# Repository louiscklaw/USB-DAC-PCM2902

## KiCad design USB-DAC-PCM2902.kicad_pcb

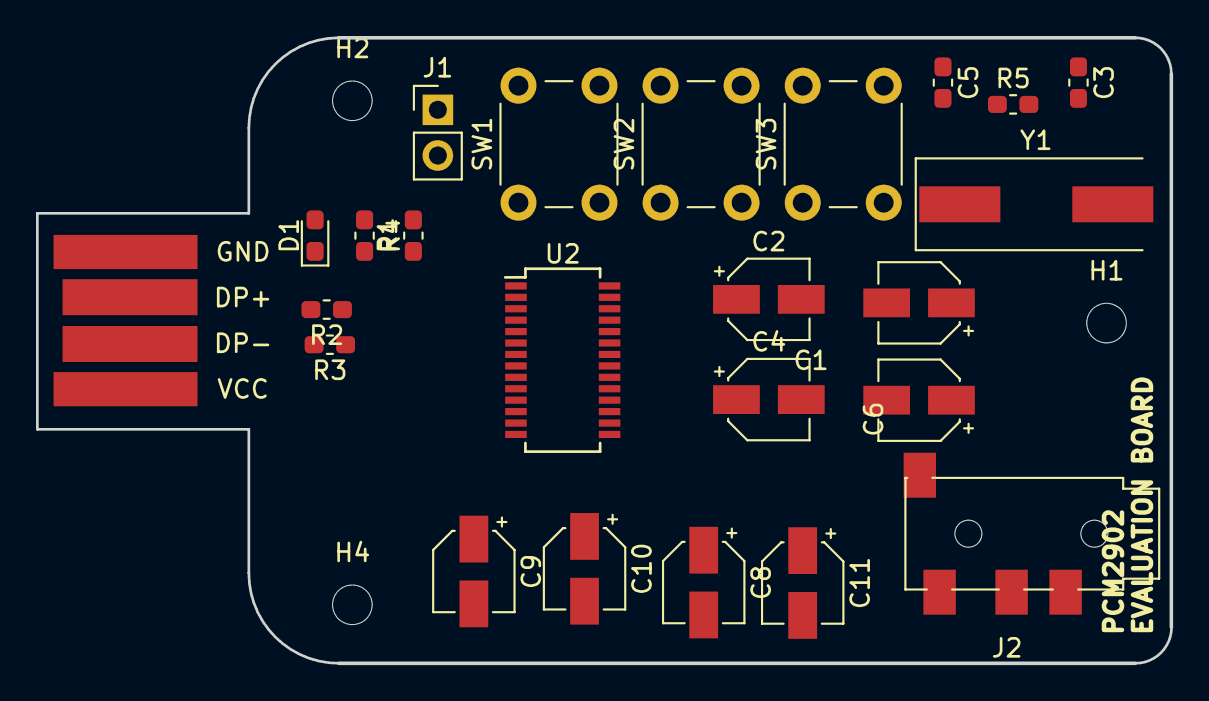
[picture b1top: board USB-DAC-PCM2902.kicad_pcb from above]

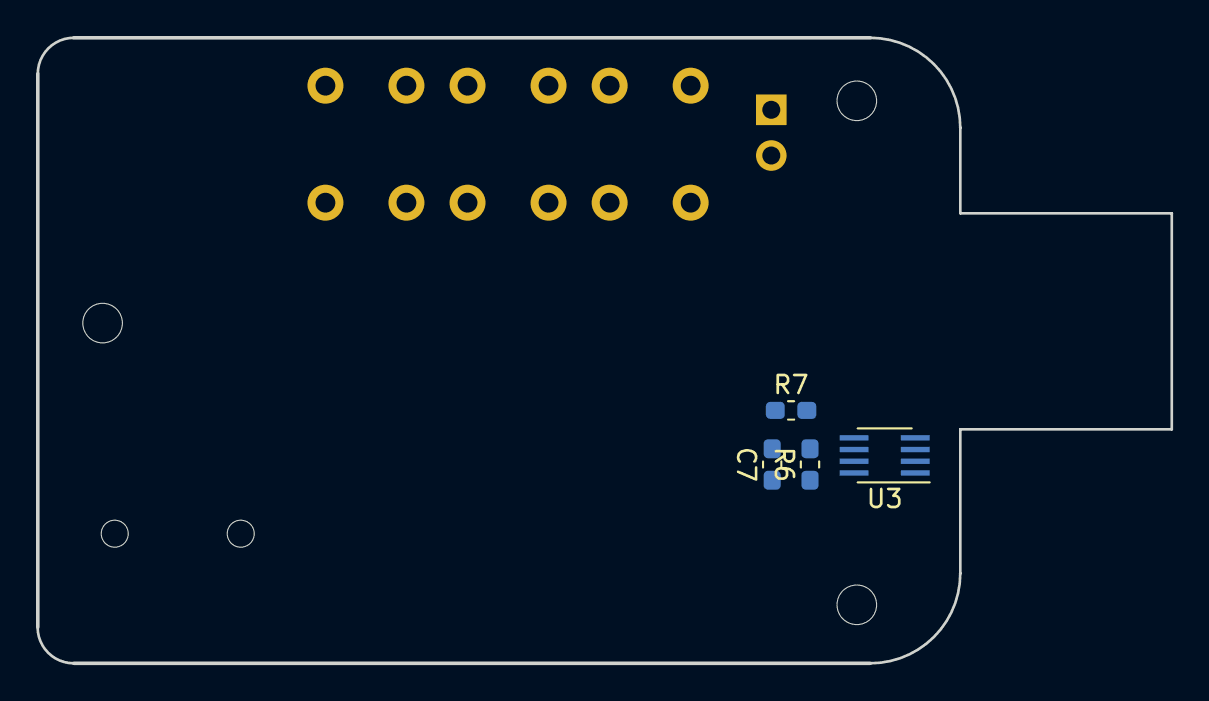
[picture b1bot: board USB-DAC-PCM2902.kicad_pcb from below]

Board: 2 copper layers, 63.0 x 34.8 mm, 32 parts (4 on the bottom side), 25 nets, no tracks yet.

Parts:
C1, C2, C4, C6: CP1uf,50V; CP_Elec_4x5.3
C3, C5: C22pf,0603; C_0603_1608Metric_Pad1.05x0.95mm_HandSolder
C7: C103,0603; C_0603_1608Metric_Pad1.05x0.95mm_HandSolder
C8, C9, C10, C11: CP10uf,16V; CP_Elec_4x5.3
D1: LED_GREEN; LED_0603_1608Metric_Pad1.05x0.95mm_HandSolder
H1, H2, H3, H4: MOUNT_M3; MountingHole_2.2mm_M2_DIN965
J1: Conn_01x02; PinHeader_1x02_P2.54mm_Vertical
J2: PJ-320D; PJ320D_3.5mm_Jack
R1: R152,0603; R_0603_1608Metric_Pad1.05x0.95mm_HandSolder
R2, R3: R220,0603; R_0603_1608Metric_Pad1.05x0.95mm_HandSolder
R4: R681,0603; R_0603_1608Metric_Pad1.05x0.95mm_HandSolder
R5: R106,0603; R_0603_1608Metric_Pad1.05x0.95mm_HandSolder
R6: R184,0603; R_0603_1608Metric_Pad1.05x0.95mm_HandSolder
R7: R913,0603; R_0603_1608Metric_Pad1.05x0.95mm_HandSolder
SW1: MUTE; SW_PUSH_6mm_H4.3mm
SW2: VOL_DOWN; SW_PUSH_6mm_H4.3mm
SW3: VOL_UP; SW_PUSH_6mm_H4.3mm
U1: USB_PCB; usb-PCB
U2: PCM2902; SSOP-28_3.9x9.9mm_P0.635mm
U3: LP2951CM; SSOP-8_2.95x2.8mm_P0.65mm
Y1: O12M; Crystal_SMD_HC49-SD

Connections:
/OUTL: C8.2, J2.3
/OUTR: C11.2, J2.2
/PIN28: SW1.2, SW2.2, SW3.2, U2.28
/VOL_DOWN: SW2.1, U2.6
/VOL_MUTE: SW1.1, U2.5
/VOL_UP: SW3.1, U2.7
GND: C1.2, C2.2, C3.1, C4.2, C5.1, C6.2, C9.2, C10.2, D1.1, J1.1, R7.2, U1.4, U2.4, U2.11, U2.12, U2.13, U2.18, U2.22, U2.24, U2.26, U3.4
unnamed: C1.1, R1.1, U2.8, U2.9, U2.27
unnamed: C2.1, U2.23
unnamed: C3.2, R5.2, U2.20, Y1.2
unnamed: C4.1, U2.19
unnamed: C5.2, R5.1, U2.21, Y1.1
unnamed: C6.1, U2.17
unnamed: C7.1, C9.1, R6.1, U2.10, U3.1
unnamed: C7.2, R6.2, R7.1, U3.7
unnamed: C8.1, U2.16
unnamed: C10.1, U2.14
unnamed: C11.1, U2.15
unnamed: D1.2, R4.1
unnamed: J1.2, U2.25
unnamed: R1.2, R2.2, U1.3
unnamed: R2.1, U2.1
unnamed: R3.1, U2.2
unnamed: R3.2, U1.2
unnamed: R4.2, U1.1, U2.3, U3.8

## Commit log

2018-11-20 update,
2018-11-21 update, draft route done,
2018-11-21 update vol button,
2018-11-23 reduce vias,
2018-11-23 make vias 1.5mm,
2018-11-23 draft ok,
2018-11-24 upadte pcb shape,
2018-11-24 upadte,
2018-11-24 upadte svg,
2020-05-07 ci: init travis token,
2020-05-07 ci: init travis build config,
